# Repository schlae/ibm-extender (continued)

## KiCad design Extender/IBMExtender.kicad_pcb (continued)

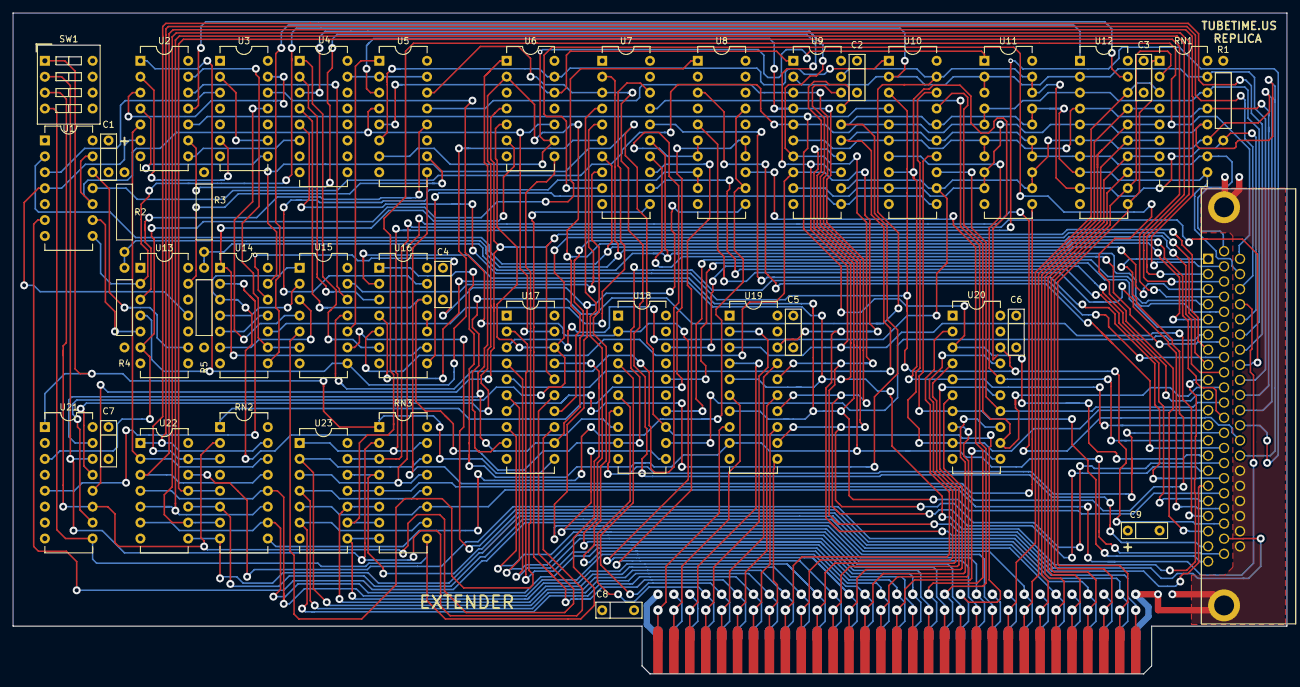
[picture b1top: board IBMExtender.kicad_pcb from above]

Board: 4 copper layers, 203.2 x 105.4 mm, 43 parts (0 on the bottom side), 158 nets.

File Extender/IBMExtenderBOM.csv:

Item,Qty,Reference(s),Value,LibPart,Footprint,Mouser
1,2,"C1, C9",10uF,device:CP1_Small,Passive:C_Disc_D0.2in_W0.1in_P0.2in,581-TAP106K016CRS 
2,7,"C2, C3, C4, C5, C6, C7, C8",0.1uF,device:C_Small,Passive:C_Disc_D0.2in_W0.1in_P0.2in,594-K104K15X7RF53H5 
3,1,J1,DB62,connectors:DB62,Conn:DB62,636-181-062-213R561
5,1,R1,4.7K,device:R,Passive:R_Axial_L0.26in_D0.92in_P0.5in_Horizontal,603-CFR-25JR-524K7 
6,2,"R2, R3",330,device:R,Passive:R_Axial_L0.26in_D0.92in_P0.5in_Horizontal,603-CFR-25JR-52330R 
7,2,"R4, R5",220,device:R,Passive:R_Axial_L0.26in_D0.92in_P0.5in_Horizontal,603-CFR-25JR-52220R 
8,1,RN1,4.7K,discretes:RPAC15_BUSSED,Active:DIP254P762X635-16,652-4116R-2LF-4.7K
9,2,"RN2, RN3",8.2K,discretes:RPAC15_BUSSED_IND,Active:DIP254P762X635-16,652-4116R-2LF-10K 
10,1,SW1,SW_DIP_x04,switches:SW_DIP_x04,Buttons_Switches_THT:SW_DIP_x4_W7.62mm_Slide,774-2064 
11,1,U1,74LS125,74xx:74LS125,Active:DIP254P762X635-14,595-SN74LS125AN 
12,1,U2,74S08,74xx:74LS08,Active:DIP254P762X635-14,595-SN74S08N 
13,1,U3,74S74,74xx:74LS74,Active:DIP254P762X635-14,595-SN74S74N 
14,1,U4,74LS138,74xx:74LS138,Active:DIP254P762X635-16,595-SN74LS138N 
15,1,U5,74LS155,74xx:74LS155,Active:DIP254P762X635-16,595-SN74LS155AN 
16,1,U6,74LS20,74xx:74LS20,Active:DIP254P762X635-14,595-SN74LS20N 
17,6,"U7, U8, U17, U18, U19, U20",74LS244,74xx:74LS244,Active:DIP254P762X635-20,595-SN74LS244N 
18,3,"U9, U10, U11",74LS374,74xx:74LS374,Active:DIP254P762X635-20,595-SN74LS374N 
19,1,U12,74LS245,74xx:74LS245,Active:DIP254P762X635-20,595-SN74LS245N 
20,1,U13,74LS74,74xx:74LS74,Active:DIP254P762X635-14,595-SN74LS74AN 
21,1,U14,74LS00,74xx:74LS00,Active:DIP254P762X635-14,595-SN74LS00N 
22,1,U15,74LS04,74xx:74LS04,Active:DIP254P762X635-14,595-SN74LS04N 
23,1,U16,74LS32,74xx:74LS32,Active:DIP254P762X635-14,595-SN74LS32N 
24,1,U21,74S85,74xx:74LS85,Active:DIP254P762X635-16,595-SN74LS85N 
25,2,"U22, U23",SN7417,logic:SN7417,Active:DIP254P762X635-14,595-SN7417N

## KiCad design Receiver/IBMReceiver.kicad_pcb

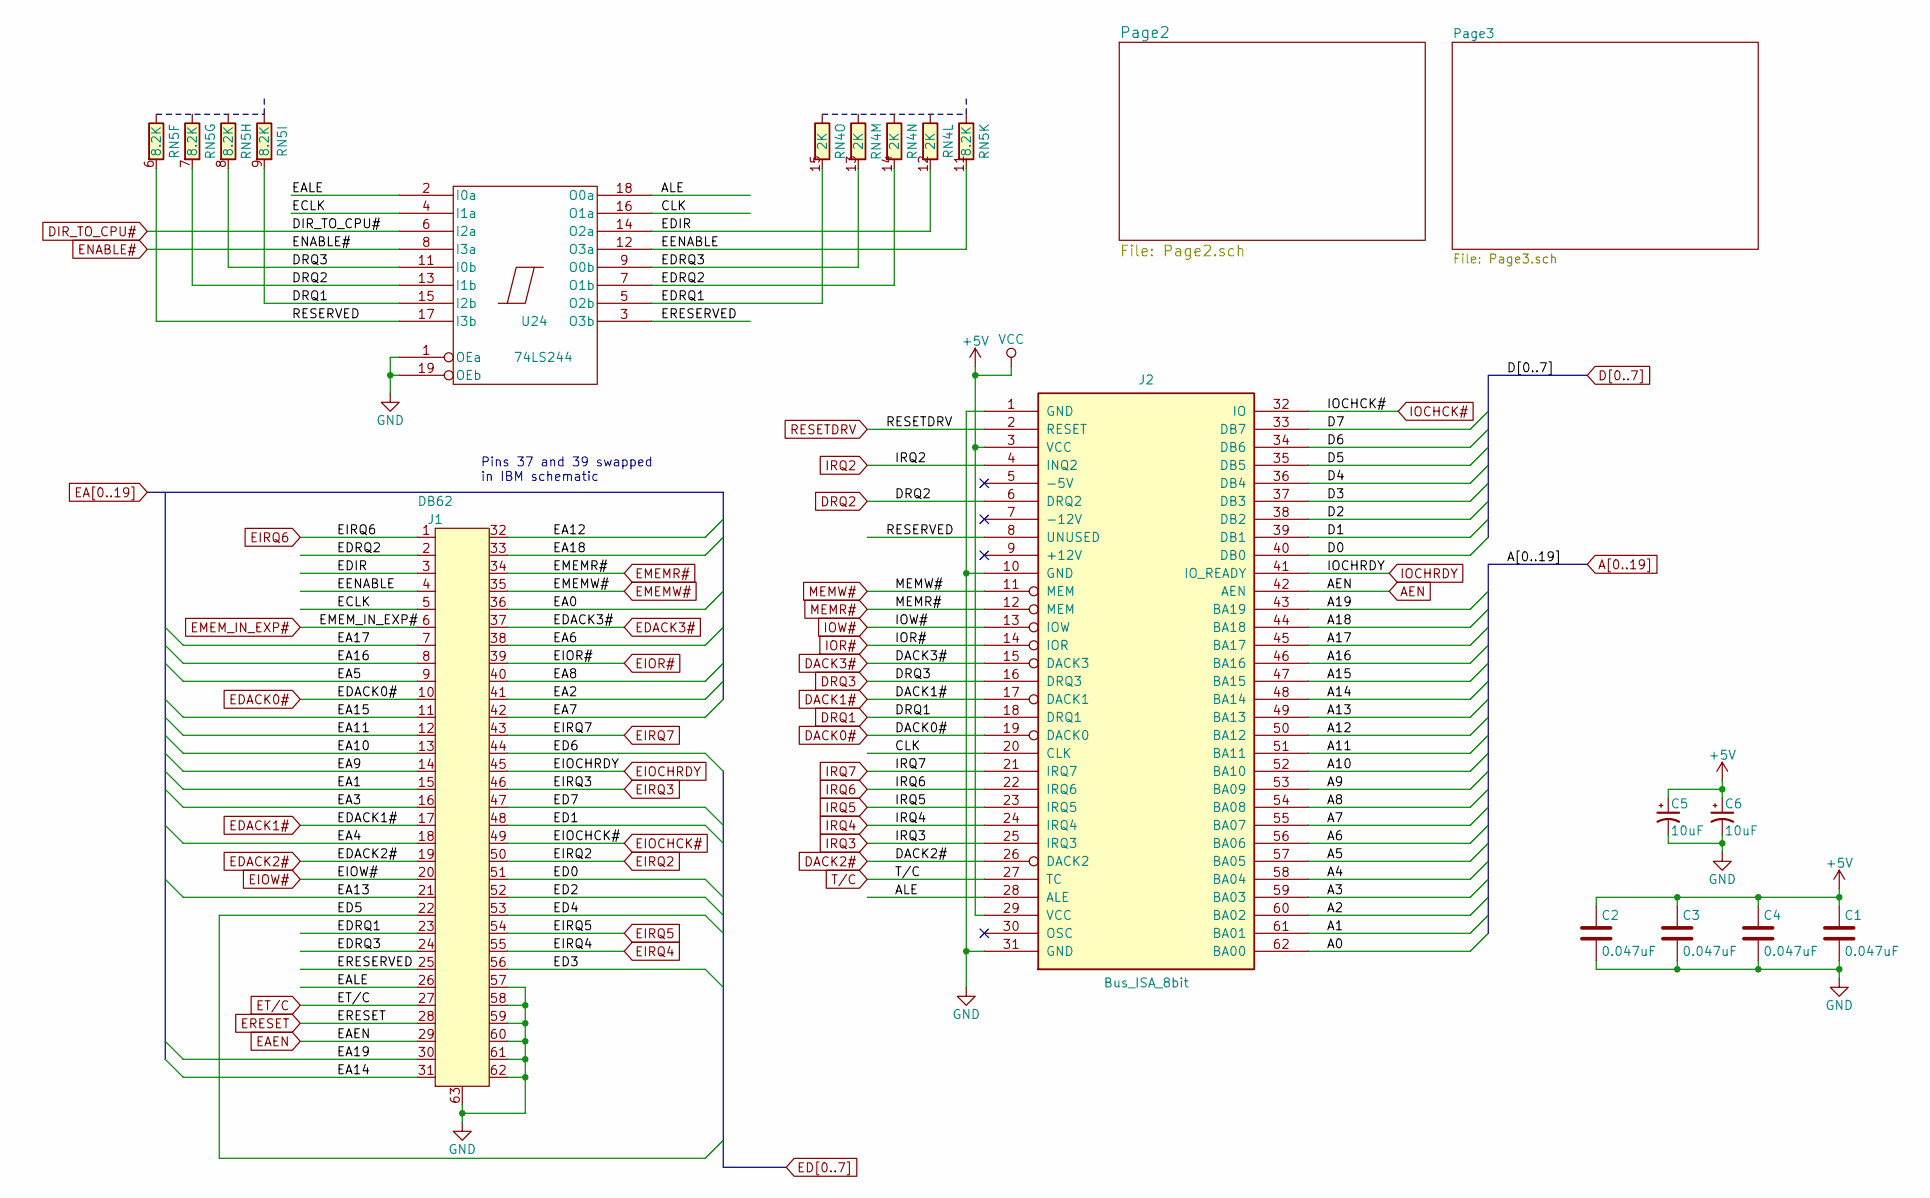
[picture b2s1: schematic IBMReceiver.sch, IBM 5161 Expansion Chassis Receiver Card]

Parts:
C1, C2, C3, C4: 0.047uF; C_Disc_D0.2in_W0.1in_P0.2in
C5, C6: 10uF; C_Disc_D0.2in_W0.1in_P0.2in
J1: DB62
J2: Bus_ISA_8bit; BUS_PC
RN4: 2K; DIP254P762X635-16
RN5: 8.2K; DIP254P762X635-16
U24: 74LS244; DIP254P762X635-20

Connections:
+5V: C1.1, C2.1, C3.1, C4.1, C5.1, C6.1, J2.3 (VCC), J2.29 (VCC), U24.20 (VCC); also elsewhere on the board
/ALE: J2.28 (ALE), U24.18 (O0a)
/CLK: J2.20 (CLK), U24.16 (O1a)
/EALE: J1.26, U24.2 (I0a)
/ECLK: J1.5, U24.4 (I1a)
/EDIR: J1.3, RN4.12, U24.14 (O2a)
/EDRQ1: J1.23, RN4.15, U24.5 (O2b)
/EDRQ2: J1.2, RN4.14, U24.7 (O1b)
/EDRQ3: J1.24, RN4.13, U24.9 (O0b)
/EENABLE: J1.4, RN5.11, U24.12 (O3a)
/ERESERVED: J1.25, U24.3 (O3b)
/RESERVED: J2.8 (UNUSED), RN5.6, U24.17 (I3b)
A0: J2.62 (BA00); also elsewhere on the board
A1: J2.61 (BA01); also elsewhere on the board
A2: J2.60 (BA02); also elsewhere on the board
A3: J2.59 (BA03); also elsewhere on the board
A4: J2.58 (BA04); also elsewhere on the board
A5: J2.57 (BA05); also elsewhere on the board
A6: J2.56 (BA06); also elsewhere on the board
A7: J2.55 (BA07); also elsewhere on the board
A8: J2.54 (BA08); also elsewhere on the board
A9: J2.53 (BA09); also elsewhere on the board
A10: J2.52 (BA10); also elsewhere on the board
A11: J2.51 (BA11); also elsewhere on the board
A12: J2.50 (BA12); also elsewhere on the board
A13: J2.49 (BA13); also elsewhere on the board
A14: J2.48 (BA14); also elsewhere on the board
A15: J2.47 (BA15); also elsewhere on the board
A16: J2.46 (BA16); also elsewhere on the board
A17: J2.45 (BA17); also elsewhere on the board
A18: J2.44 (BA18); also elsewhere on the board
A19: J2.43 (BA19); also elsewhere on the board
AEN: J2.42 (AEN); also elsewhere on the board
D0: J2.40 (DB0); also elsewhere on the board
D1: J2.39 (DB1); also elsewhere on the board
D2: J2.38 (DB2); also elsewhere on the board
D3: J2.37 (DB3); also elsewhere on the board
D4: J2.36 (DB4); also elsewhere on the board
D5: J2.35 (DB5); also elsewhere on the board
D6: J2.34 (DB6); also elsewhere on the board
D7: J2.33 (DB7); also elsewhere on the board
DACK0#: J2.19 (DACK0); also elsewhere on the board
DACK1#: J2.17 (DACK1); also elsewhere on the board
DACK2#: J2.26 (DACK2); also elsewhere on the board
DACK3#: J2.15 (DACK3); also elsewhere on the board
DIR_TO_CPU#: U24.6 (I2a); also elsewhere on the board
DRQ1: J2.18 (DRQ1), RN5.9, U24.15 (I2b); also elsewhere on the board
DRQ2: J2.6 (DRQ2), RN5.7, U24.13 (I1b); also elsewhere on the board
DRQ3: J2.16 (DRQ3), RN5.8, U24.11 (I0b); also elsewhere on the board
EA0: J1.36; also elsewhere on the board
EA1: J1.15; also elsewhere on the board
EA2: J1.41; also elsewhere on the board
EA3: J1.16; also elsewhere on the board
EA4: J1.18; also elsewhere on the board
EA5: J1.9; also elsewhere on the board
EA6: J1.38; also elsewhere on the board
EA7: J1.42; also elsewhere on the board
EA8: J1.40; also elsewhere on the board
EA9: J1.14; also elsewhere on the board
EA10: J1.13; also elsewhere on the board
EA11: J1.12; also elsewhere on the board
EA12: J1.32; also elsewhere on the board
EA13: J1.21; also elsewhere on the board
EA14: J1.31; also elsewhere on the board
EA15: J1.11; also elsewhere on the board
EA16: J1.8; also elsewhere on the board
EA17: J1.7; also elsewhere on the board
EA18: J1.33; also elsewhere on the board
EA19: J1.30; also elsewhere on the board
EAEN: J1.29; also elsewhere on the board
ED0: J1.51; also elsewhere on the board
ED1: J1.48; also elsewhere on the board
ED2: J1.52; also elsewhere on the board
ED3: J1.56; also elsewhere on the board
ED4: J1.53; also elsewhere on the board
ED5: J1.22; also elsewhere on the board
ED6: J1.44; also elsewhere on the board
ED7: J1.47; also elsewhere on the board
EDACK0#: J1.10; also elsewhere on the board
EDACK1#: J1.17; also elsewhere on the board
EDACK2#: J1.19; also elsewhere on the board
EDACK3#: J1.37; also elsewhere on the board
EIOCHCK#: J1.49; also elsewhere on the board
EIOCHRDY: J1.45; also elsewhere on the board
EIOR#: J1.39; also elsewhere on the board
EIOW#: J1.20; also elsewhere on the board
EIRQ2: J1.50; also elsewhere on the board
EIRQ3: J1.46; also elsewhere on the board
EIRQ4: J1.55; also elsewhere on the board
EIRQ5: J1.54; also elsewhere on the board
EIRQ6: J1.1; also elsewhere on the board
EIRQ7: J1.43; also elsewhere on the board
EMEMR#: J1.34; also elsewhere on the board
EMEMW#: J1.35; also elsewhere on the board
EMEM_IN_EXP#: J1.6; also elsewhere on the board
ENABLE#: U24.8 (I3a); also elsewhere on the board
ERESET: J1.28; also elsewhere on the board
ET/C: J1.27; also elsewhere on the board
GND: C1.2, C2.2, C3.2, C4.2, C5.2, C6.2, J1.57, J1.58, J1.59, J1.60, J1.61, J1.62, J1.63, J2.1 (GND), J2.10 (GND), J2.31 (GND), U24.1 (OEa), U24.10 (GND), U24.19 (OEb); also elsewhere on the board
IOCHCK#: J2.32 (IO); also elsewhere on the board
IOCHRDY: J2.41 (IO_READY); also elsewhere on the board
IOR#: J2.14 (IOR); also elsewhere on the board
IOW#: J2.13 (IOW); also elsewhere on the board
IRQ2: J2.4 (INQ2); also elsewhere on the board
IRQ3: J2.25 (IRQ3); also elsewhere on the board
IRQ4: J2.24 (IRQ4); also elsewhere on the board
IRQ5: J2.23 (IRQ5); also elsewhere on the board
IRQ6: J2.22 (IRQ6); also elsewhere on the board
IRQ7: J2.21 (IRQ7); also elsewhere on the board
MEMR#: J2.12 (MEM); also elsewhere on the board
MEMW#: J2.11 (MEM); also elsewhere on the board
RESETDRV: J2.2 (RESET); also elsewhere on the board
T/C: J2.27 (TC); also elsewhere on the board

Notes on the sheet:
Pins 37 and 39 swapped in IBM schematic

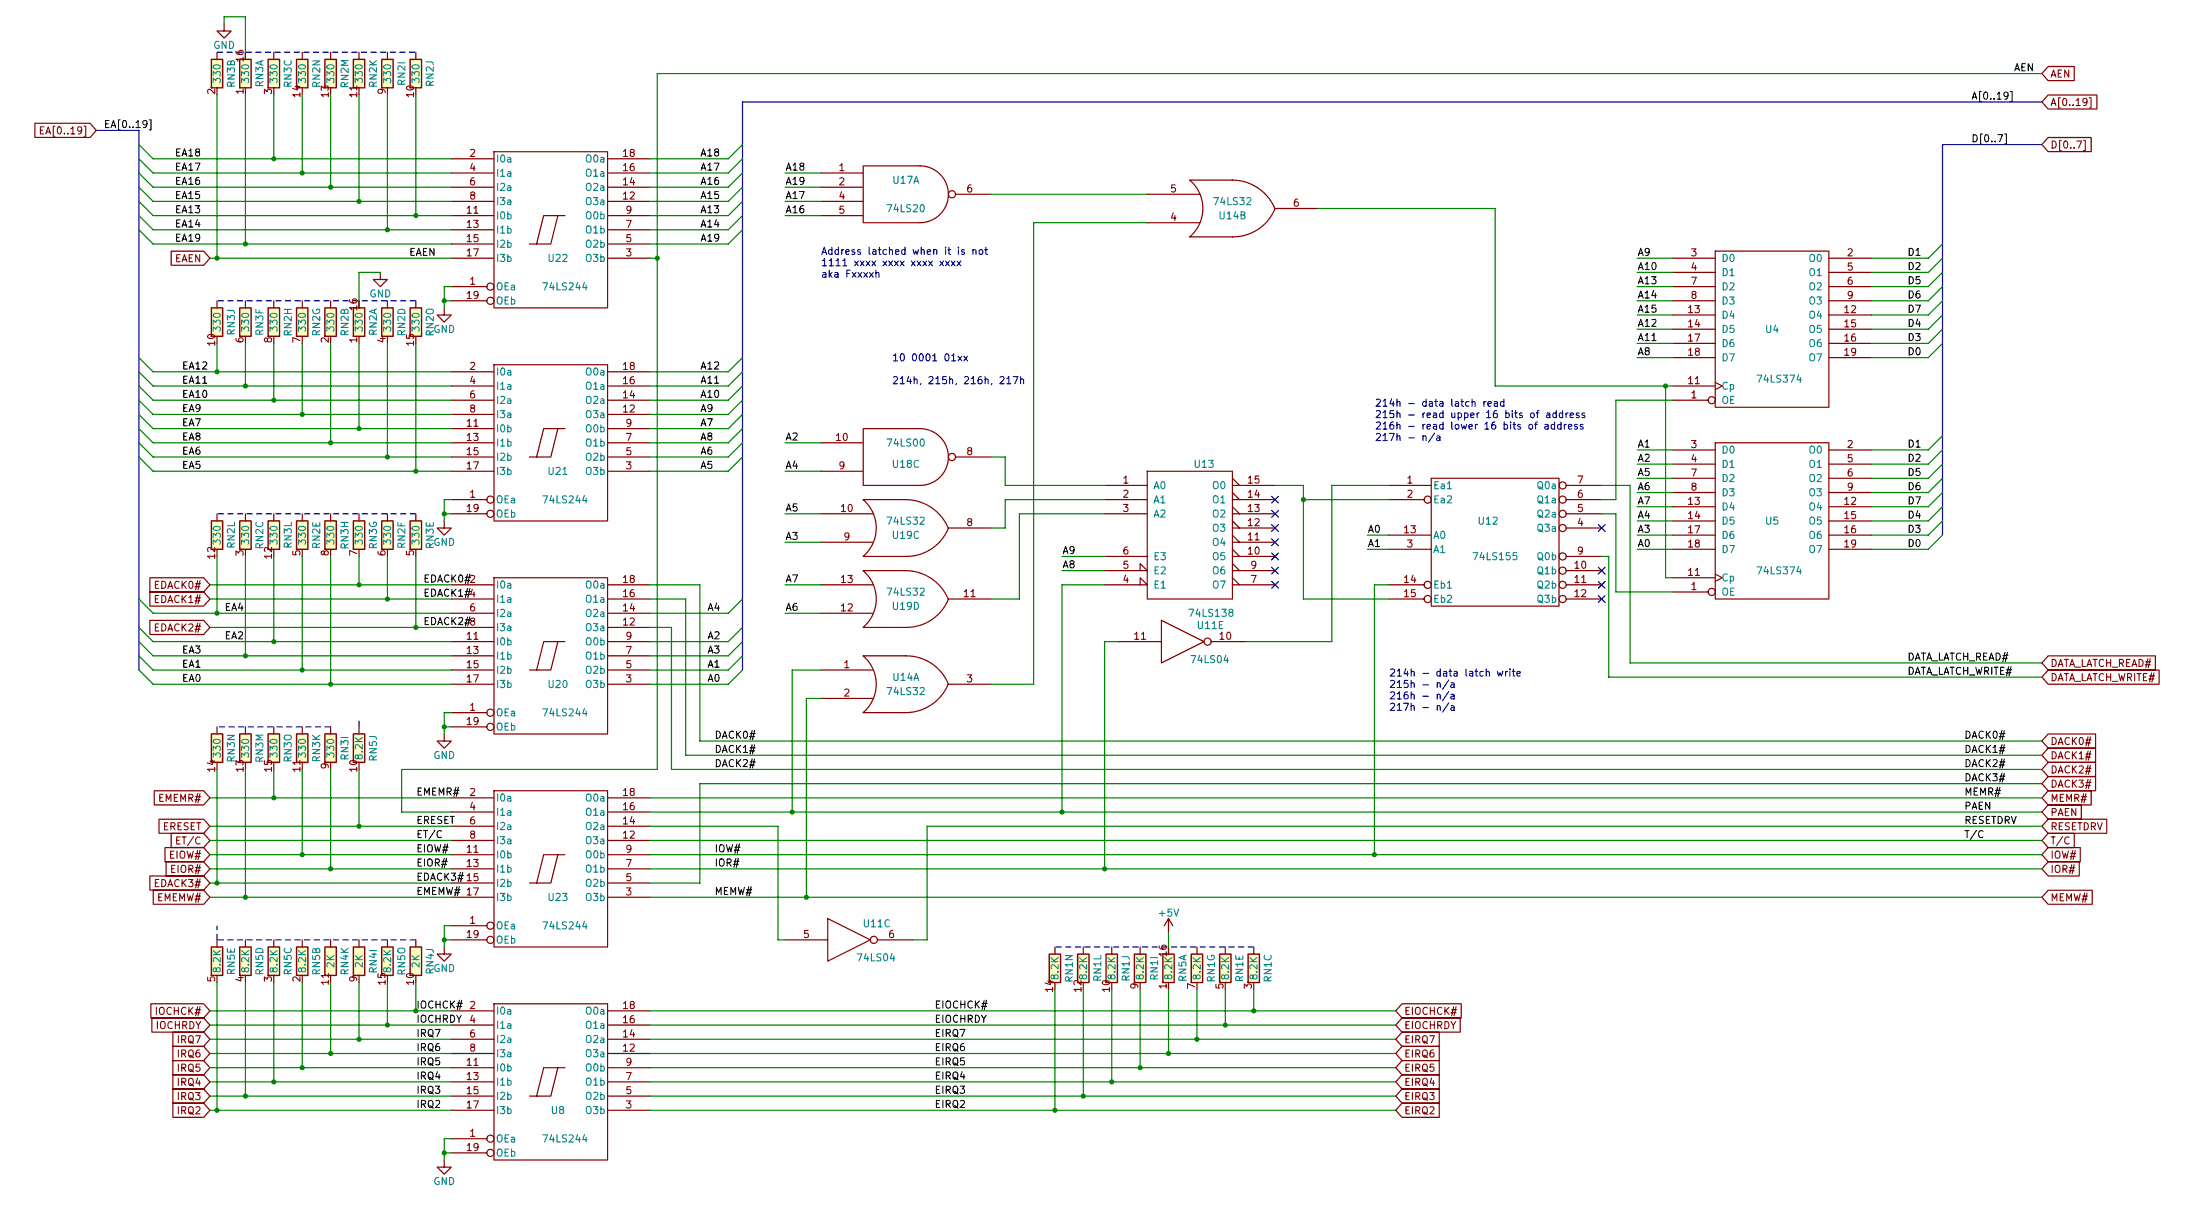
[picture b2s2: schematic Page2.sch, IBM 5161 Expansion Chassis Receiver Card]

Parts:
RN1, RN5: 8.2K; DIP254P762X635-16
RN2, RN3: 330; DIP254P762X635-16
RN4: 2K; DIP254P762X635-16
U4, U5: 74LS374; DIP254P762X635-20
U8, U20, U21, U22, U23: 74LS244; DIP254P762X635-20
U11: 74LS04; DIP254P762X635-14
U12: 74LS155; DIP254P762X635-16
U13: 74LS138; DIP254P762X635-16
U14, U19: 74LS32; DIP254P762X635-14
U17: 74LS20; DIP254P762X635-14
U18: 74LS00; DIP254P762X635-14

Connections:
+5V: RN5.16, U4.20 (VCC), U5.20 (VCC), U8.20 (VCC), U11.14 (VCC), U12.16 (VCC), U13.16 (VCC), U14.14 (VCC), U17.14 (VCC), U18.14 (VCC), U19.14 (VCC), U20.20 (VCC), U21.20 (VCC), U22.20 (VCC), U23.20 (VCC); also elsewhere on the board
A0: U5.18 (D7), U12.13 (A0), U20.3 (O3b); also elsewhere on the board
A1: U5.3 (D0), U12.3 (A1), U20.5 (O2b); also elsewhere on the board
A2: U5.4 (D1), U18.10, U20.9 (O0b); also elsewhere on the board
A3: U5.17 (D6), U19.9, U20.7 (O1b); also elsewhere on the board
A4: U5.14 (D5), U18.9, U20.14 (O2a); also elsewhere on the board
A5: U5.7 (D2), U19.10, U21.3 (O3b); also elsewhere on the board
A6: U5.8 (D3), U19.12, U21.5 (O2b); also elsewhere on the board
A7: U5.13 (D4), U19.13, U21.9 (O0b); also elsewhere on the board
A8: U4.18 (D7), U13.5 (E2), U21.7 (O1b); also elsewhere on the board
A9: U4.3 (D0), U13.6 (E3), U21.12 (O3a); also elsewhere on the board
A10: U4.4 (D1), U21.14 (O2a); also elsewhere on the board
A11: U4.17 (D6), U21.16 (O1a); also elsewhere on the board
A12: U4.14 (D5), U21.18 (O0a); also elsewhere on the board
A13: U4.7 (D2), U22.9 (O0b); also elsewhere on the board
A14: U4.8 (D3), U22.7 (O1b); also elsewhere on the board
A15: U4.13 (D4), U22.12 (O3a); also elsewhere on the board
A16: U17.5, U22.14 (O2a); also elsewhere on the board
A17: U17.4, U22.16 (O1a); also elsewhere on the board
A18: U17.1, U22.18 (O0a); also elsewhere on the board
A19: U17.2, U22.5 (O2b); also elsewhere on the board
AEN: U22.3 (O3b), U23.4 (I1a); also elsewhere on the board
D0: U4.19 (O7), U5.19 (O7); also elsewhere on the board
D1: U4.2 (O0), U5.2 (O0); also elsewhere on the board
D2: U4.5 (O1), U5.5 (O1); also elsewhere on the board
D3: U4.16 (O6), U5.16 (O6); also elsewhere on the board
D4: U4.15 (O5), U5.15 (O5); also elsewhere on the board
D5: U4.6 (O2), U5.6 (O2); also elsewhere on the board
D6: U4.9 (O3), U5.9 (O3); also elsewhere on the board
D7: U4.12 (O4), U5.12 (O4); also elsewhere on the board
DACK0#: U20.18 (O0a); also elsewhere on the board
DACK1#: U20.16 (O1a); also elsewhere on the board
DACK2#: U20.12 (O3a); also elsewhere on the board
DACK3#: U23.5 (O2b); also elsewhere on the board
DATA_LATCH_READ#: U12.7 (Q0a); also elsewhere on the board
DATA_LATCH_WRITE#: U12.9 (Q0b); also elsewhere on the board
EA0: RN3.8, U20.17 (I3b); also elsewhere on the board
EA1: RN2.5, U20.15 (I2b); also elsewhere on the board
EA2: RN3.12, U20.11 (I0b); also elsewhere on the board
EA3: RN2.3, U20.13 (I1b); also elsewhere on the board
EA4: RN2.12, U20.6 (I2a); also elsewhere on the board
EA5: RN2.15, U21.17 (I3b); also elsewhere on the board
EA6: RN2.4, U21.15 (I2b); also elsewhere on the board
EA7: RN2.1, U21.11 (I0b); also elsewhere on the board
EA8: RN2.2, U21.13 (I1b); also elsewhere on the board
EA9: RN2.7, U21.8 (I3a); also elsewhere on the board
EA10: RN2.8, U21.6 (I2a); also elsewhere on the board
EA11: RN3.6, U21.4 (I1a); also elsewhere on the board
EA12: RN3.10, U21.2 (I0a); also elsewhere on the board
EA13: RN2.10, U22.11 (I0b); also elsewhere on the board
EA14: RN2.9, U22.13 (I1b); also elsewhere on the board
EA15: RN2.11, U22.8 (I3a); also elsewhere on the board
EA16: RN2.13, U22.6 (I2a); also elsewhere on the board
EA17: RN2.14, U22.4 (I1a); also elsewhere on the board
EA18: RN3.3, U22.2 (I0a); also elsewhere on the board
EA19: RN3.1, U22.15 (I2b); also elsewhere on the board
EAEN: RN3.2, U22.17 (I3b); also elsewhere on the board
EDACK0#: RN3.7, U20.2 (I0a); also elsewhere on the board
EDACK1#: RN2.6, U20.4 (I1a); also elsewhere on the board
EDACK2#: RN3.5, U20.8 (I3a); also elsewhere on the board
EDACK3#: RN3.14, U23.15 (I2b); also elsewhere on the board
EIOCHCK#: RN1.3, U8.18 (O0a); also elsewhere on the board
EIOCHRDY: RN1.5, U8.16 (O1a); also elsewhere on the board
EIOR#: RN3.9, U23.13 (I1b); also elsewhere on the board
EIOW#: RN3.11, U23.11 (I0b); also elsewhere on the board
EIRQ2: RN1.14, U8.3 (O3b); also elsewhere on the board
EIRQ3: RN1.12, U8.5 (O2b); also elsewhere on the board
EIRQ4: RN1.10, U8.7 (O1b); also elsewhere on the board
EIRQ5: RN1.9, U8.9 (O0b); also elsewhere on the board
EIRQ6: RN5.1, U8.12 (O3a); also elsewhere on the board
EIRQ7: RN1.7, U8.14 (O2a); also elsewhere on the board
EMEMR#: RN3.15, U23.2 (I0a); also elsewhere on the board
EMEMW#: RN3.13, U23.17 (I3b); also elsewhere on the board
ERESET: RN5.10, U23.6 (I2a); also elsewhere on the board
ET/C: U23.8 (I3a); also elsewhere on the board
GND: RN2.16, RN3.16, U4.10 (GND), U5.10 (GND), U8.1 (OEa), U8.10 (GND), U8.19 (OEb), U11.7 (GND), U12.8 (GND), U13.8 (GND), U14.7 (GND), U17.7 (GND), U18.7 (GND), U19.7 (GND), U20.1 (OEa), U20.10 (GND), U20.19 (OEb), U21.1 (OEa), U21.10 (GND), U21.19 (OEb), U22.1 (OEa), U22.10 (GND), U22.19 (OEb), U23.1 (OEa), U23.10 (GND), U23.19 (OEb); also elsewhere on the board
IOCHCK#: RN4.10, U8.2 (I0a); also elsewhere on the board
IOCHRDY: RN5.15, U8.4 (I1a); also elsewhere on the board
IOR#: U11.11, U23.7 (O1b); also elsewhere on the board
IOW#: U12.14 (Eb1), U23.9 (O0b); also elsewhere on the board
IRQ2: RN5.5, U8.17 (I3b); also elsewhere on the board
IRQ3: RN5.4, U8.15 (I2b); also elsewhere on the board
IRQ4: RN5.3, U8.13 (I1b); also elsewhere on the board
IRQ5: RN5.2, U8.11 (I0b); also elsewhere on the board
IRQ6: RN4.11, U8.8 (I3a); also elsewhere on the board
IRQ7: RN4.9, U8.6 (I2a); also elsewhere on the board
MEMR#: U23.18 (O0a); also elsewhere on the board
MEMW#: U14.2, U23.3 (O3b); also elsewhere on the board
unnamed: U11.5, U23.14 (O2a)
unnamed: U11.10, U12.1 (Ea1)
unnamed: U5.1 (OE), U12.5 (Q2a)
unnamed: U4.1 (OE), U12.6 (Q1a)
unnamed: U12.2 (Ea2), U12.15 (Eb2), U13.15 (O0)
unnamed: U13.1 (A0), U18.8
unnamed: U13.2 (A1), U19.8
unnamed: U13.3 (A2), U19.11
unnamed: U14.3, U14.4
unnamed: U14.5, U17.6
unnamed: U4.11 (Cp), U5.11 (Cp), U14.6
PAEN: U13.4 (E1), U14.1, U23.16 (O1a); also elsewhere on the board
RESETDRV: U11.6; also elsewhere on the board
T/C: U23.12 (O3a); also elsewhere on the board

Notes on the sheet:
10 0001 01xx 214h, 215h, 216h, 217h
Address latched when it is not 1111 xxxx xxxx xxxx xxxx aka Fxxxxh
214h - data latch read 215h - read upper 16 bits of address 216h - read lower 16 bits of address 217h - n/a
214h - data latch write 215h - n/a 216h - n/a 217h - n/a

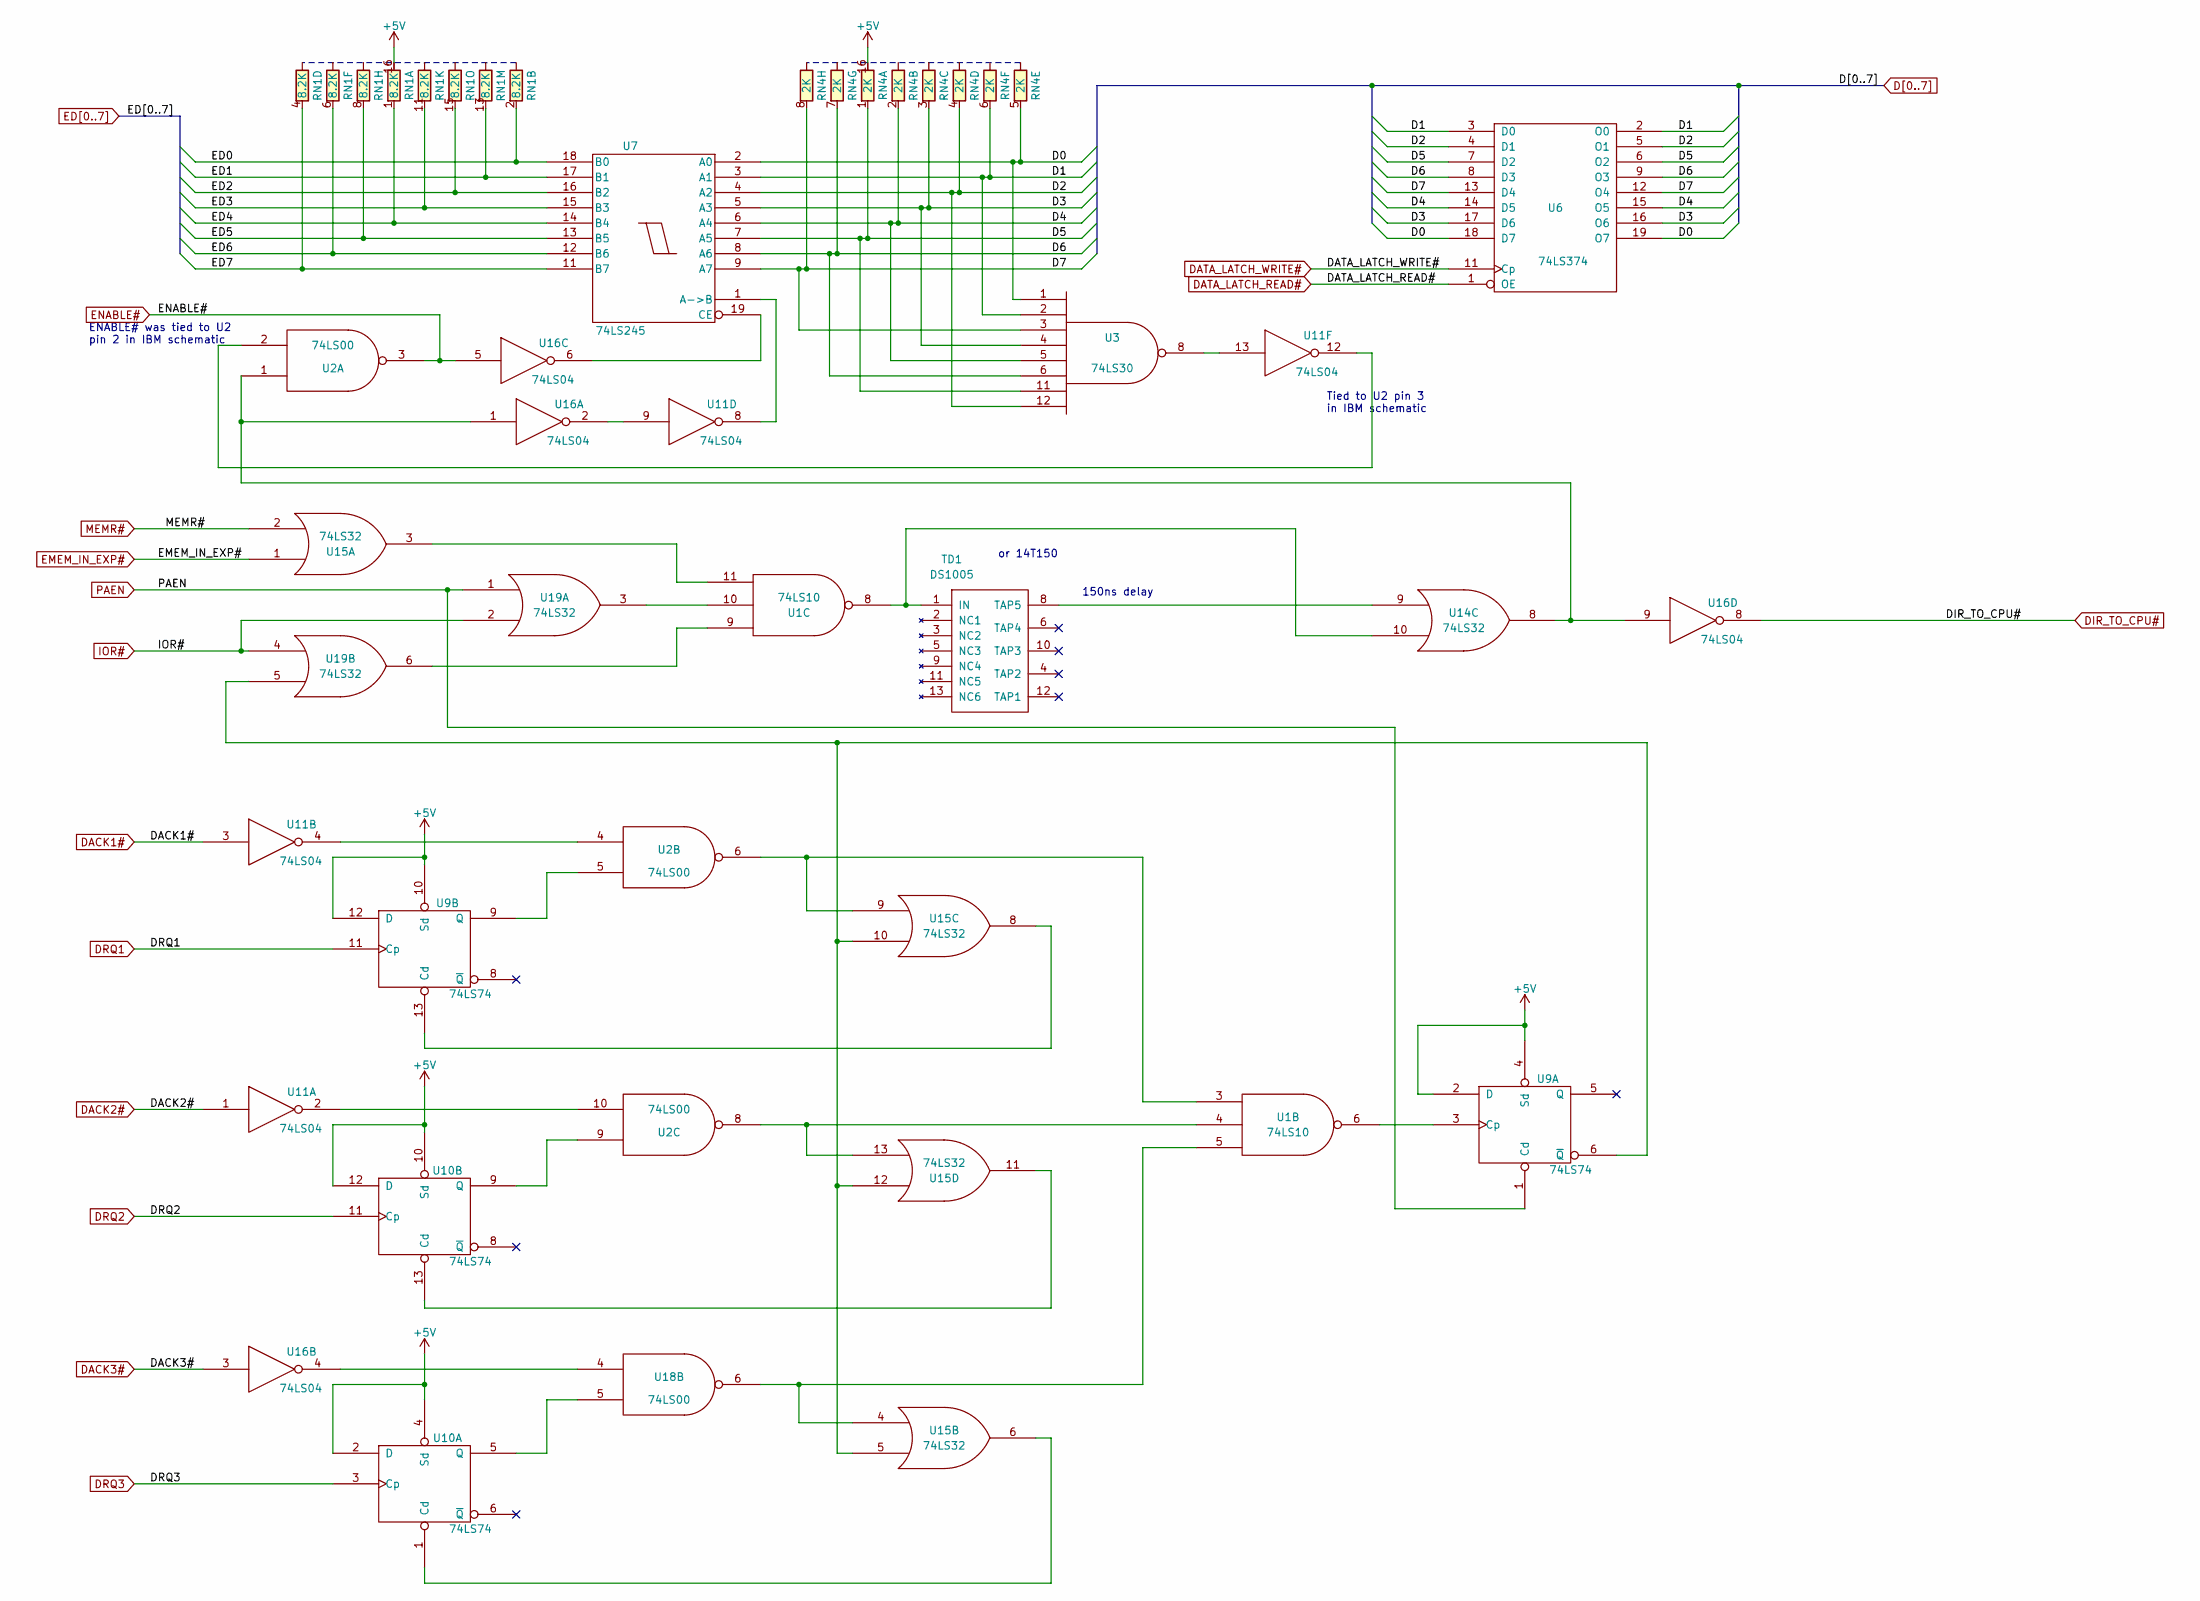
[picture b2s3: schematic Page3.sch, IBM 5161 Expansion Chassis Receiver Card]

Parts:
RN1: 8.2K; DIP254P762X635-16
RN4: 2K; DIP254P762X635-16
TD1: DS1005; DIP254P762X635-14
U1: 74LS10; DIP254P762X635-14
U2, U18: 74LS00; DIP254P762X635-14
U3: 74LS30; DIP254P762X635-14
U6: 74LS374; DIP254P762X635-20
U7: 74LS245; DIP254P762X635-20
U9, U10: 74LS74; DIP254P762X635-14
U11, U16: 74LS04; DIP254P762X635-14
U14, U15, U19: 74LS32; DIP254P762X635-14

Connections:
+5V: RN1.16, RN4.16, TD1.14 (VCC), U1.14 (VCC), U2.14 (VCC), U3.14 (VCC), U6.20 (VCC), U7.20 (VCC), U9.2 (D), U9.4 (Sd), U9.10 (Sd), U9.12 (D), U9.14 (VCC), U10.2 (D), U10.4 (Sd), U10.10 (Sd), U10.12 (D), U10.14 (VCC), U11.14 (VCC), U14.14 (VCC), U15.14 (VCC), U16.14 (VCC), U18.14 (VCC), U19.14 (VCC); also elsewhere on the board
D0: RN4.5, U3.1, U6.18 (D7), U6.19 (O7), U7.2 (A0); also elsewhere on the board
D1: RN4.6, U3.2, U6.2 (O0), U6.3 (D0), U7.3 (A1); also elsewhere on the board
D2: RN4.4, U3.12, U6.4 (D1), U6.5 (O1), U7.4 (A2); also elsewhere on the board
D3: RN4.3, U3.4, U6.16 (O6), U6.17 (D6), U7.5 (A3); also elsewhere on the board
D4: RN4.2, U3.5, U6.14 (D5), U6.15 (O5), U7.6 (A4); also elsewhere on the board
D5: RN4.1, U3.11, U6.6 (O2), U6.7 (D2), U7.7 (A5); also elsewhere on the board
D6: RN4.7, U3.6, U6.8 (D3), U6.9 (O3), U7.8 (A6); also elsewhere on the board
D7: RN4.8, U3.3, U6.12 (O4), U6.13 (D4), U7.9 (A7); also elsewhere on the board
DACK1#: U11.3; also elsewhere on the board
DACK2#: U11.1; also elsewhere on the board
DACK3#: U16.3; also elsewhere on the board
DATA_LATCH_READ#: U6.1 (OE); also elsewhere on the board
DATA_LATCH_WRITE#: U6.11 (Cp); also elsewhere on the board
DIR_TO_CPU#: U16.8; also elsewhere on the board
DRQ1: U9.11 (Cp); also elsewhere on the board
DRQ2: U10.11 (Cp); also elsewhere on the board
DRQ3: U10.3 (Cp); also elsewhere on the board
ED0: RN1.2, U7.18 (B0); also elsewhere on the board
ED1: RN1.13, U7.17 (B1); also elsewhere on the board
ED2: RN1.15, U7.16 (B2); also elsewhere on the board
ED3: RN1.11, U7.15 (B3); also elsewhere on the board
ED4: RN1.1, U7.14 (B4); also elsewhere on the board
ED5: RN1.8, U7.13 (B5); also elsewhere on the board
ED6: RN1.6, U7.12 (B6); also elsewhere on the board
ED7: RN1.4, U7.11 (B7); also elsewhere on the board
EMEM_IN_EXP#: U15.1; also elsewhere on the board
ENABLE#: U2.3, U16.5; also elsewhere on the board
GND: TD1.7 (GND), U1.7 (GND), U2.7 (GND), U3.7 (GND), U6.10 (GND), U7.10 (GND), U9.7 (GND), U10.7 (GND), U11.7 (GND), U14.7 (GND), U15.7 (GND), U16.7 (GND), U18.7 (GND), U19.7 (GND); also elsewhere on the board
IOR#: U19.2, U19.4; also elsewhere on the board
MEMR#: U15.2; also elsewhere on the board
unnamed: TD1.1 (IN), U1.8, U14.10
unnamed: TD1.8 (TAP5), U14.9
unnamed: U1.3, U2.6, U15.9
unnamed: U1.4, U2.8, U15.13
unnamed: U1.5, U15.4, U18.6
unnamed: U1.6, U9.3 (Cp)
unnamed: U1.9, U19.6
unnamed: U1.10, U19.3
unnamed: U1.11, U15.3
unnamed: U2.5, U9.9 (Q)
unnamed: U10.1 (Cd), U15.6
unnamed: U10.5 (Q), U18.5
unnamed: U2.9, U10.9 (Q)
unnamed: U10.13 (Cd), U15.11
unnamed: U2.10, U11.2
unnamed: U2.4, U11.4
unnamed: U7.1 (A->B), U11.8
unnamed: U11.9, U16.2
unnamed: U2.2, U11.12
unnamed: U3.8, U11.13
unnamed: U2.1, U14.8, U16.1, U16.9
unnamed: U9.13 (Cd), U15.8
unnamed: U9.6 (~Q), U15.5, U15.10, U15.12, U19.5
unnamed: U16.4, U18.4
unnamed: U7.19 (CE), U16.6
PAEN: U9.1 (Cd), U19.1; also elsewhere on the board

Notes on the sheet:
or 14T150
150ns delay
ENABLE# was tied to U2 pin 2 in IBM schematic
Tied to U2 pin 3 in IBM schematic

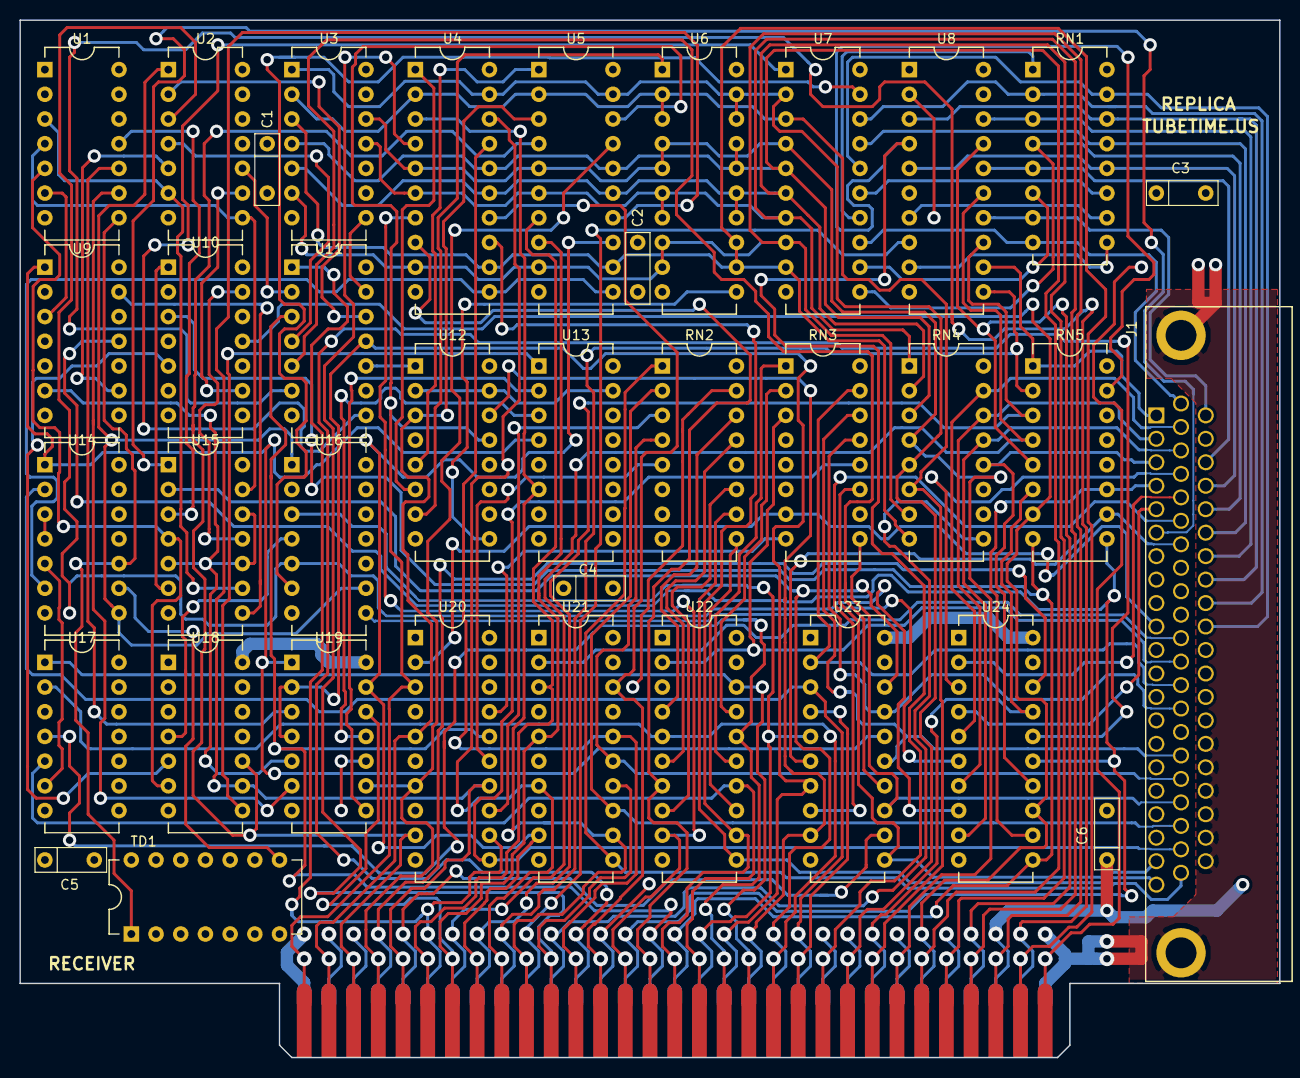
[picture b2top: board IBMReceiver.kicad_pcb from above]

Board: 4 copper layers, 129.5 x 106.7 mm, 38 parts (0 on the bottom side), 152 nets.

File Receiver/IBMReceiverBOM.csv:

Item,Qty,Reference(s),Value,LibPart,Footprint,Mouser
1,4,"C1, C2, C3, C4",0.1uF,device:C,Passive:C_Disc_D0.2in_W0.1in_P0.2in,594-K104K15X7RF53H5 
2,2,"C5, C6",10uF,device:CP1_Small,Passive:C_Disc_D0.2in_W0.1in_P0.2in,581-TAP106K016CRS 
3,1,J1,DB62,connectors:DB62,Conn:DB62,636-181-062-213R561
5,2,"RN1, RN5",8.2K,discretes:RPAC15_BUSSED_IND,Active:DIP254P762X635-16,652-4116R-2LF-10K 
6,2,"RN2, RN3",330,discretes:RPAC15_BUSSED_IND,Active:DIP254P762X635-16,652-4116R-2LF-330 
7,1,RN4,2K,discretes:RPAC15_BUSSED_IND,Active:DIP254P762X635-16,652-4116R-2LF-2K 
8,1,TD1,DS1005,logic:DS1005,Active:DIP254P762X635-14,14T150 or equiv
9,1,U1,74LS10,74xx:74LS10,Active:DIP254P762X635-14,595-SN74LS10N 
10,2,"U2, U18",74LS00,74xx:74LS00,Active:DIP254P762X635-14,595-SN74LS00N 
11,1,U3,74LS30,74xx:74LS30,Active:DIP254P762X635-14,595-SN74LS30N 
12,3,"U4, U5, U6",74LS374,74xx:74LS374,Active:DIP254P762X635-20,595-SN74LS374N 
13,1,U7,74LS245,74xx:74LS245,Active:DIP254P762X635-20,595-SN74LS245N 
14,6,"U8, U20, U21, U22, U23, U24",74LS244,74xx:74LS244,Active:DIP254P762X635-20,595-SN74LS244N 
15,2,"U9, U10",74LS74,74xx:74LS74,Active:DIP254P762X635-14,595-SN74LS74N 
16,2,"U11, U16",74LS04,74xx:74LS04,Active:DIP254P762X635-14,595-SN74LS04N 
17,1,U12,74LS155,74xx:74LS155,Active:DIP254P762X635-16,595-SN74LS155AN 
18,1,U13,74LS138,74xx:74LS138,Active:DIP254P762X635-16,595-SN74LS138N 
19,3,"U14, U15, U19",74LS32,74xx:74LS32,Active:DIP254P762X635-14,595-SN74LS32N 
20,1,U17,74LS20,74xx:74LS20,Active:DIP254P762X635-14,595-SN74LS20N

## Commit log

2018-09-05 Initial project files
2018-09-05 Add readme
2018-09-05 Add license info
2021-06-26 Add card bracket info
2023-12-29 Add reference to backplane project
